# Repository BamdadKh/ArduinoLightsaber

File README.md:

# Arduino Lightsaber

A lightsaber prop built around an Arduino Nano on a custom PCB. It has a 144-LED blade,
sound from a DFPlayer Mini, swing detection with an MPU-6050, a small OLED and two buttons.
I built it for a Halloween costume.

*The OLED screens, rendered by the firmware's own UI code in a PC simulator.*

## Hardware

| | |
|---|---|
| Microcontroller | Arduino Nano (ATmega328P) |
| Motion | GY-521 (MPU-6050) on I²C |
| Sound | DFPlayer Mini, external amplifier and speaker |
| Blade | WS2812B strip, 144 LEDs, data on D6 |
| Buttons | main on D2, aux on D3 |
| Display | 0.91" SSD1306 128×32 OLED, software I²C on D8 (SDA) and D9 (SCL) |
| Power | one 18650 cell wired to the Nano's 5V pin, no boost converter |

The pin map, bill of materials and the known problems with the V3 board are in
[docs/hardware.md](docs/hardware.md). The schematic is in
[hardware/exports](hardware/exports/lightsaber-schematic.pdf). The schematic has mistakes the
board inherited; the firmware works around them, so trust the board and `docs/hardware.md`
over the schematic.

The hilt is modelled in Fusion 360 ([lightsaber-hilt.f3z](hardware/3d/lightsaber-hilt.f3z)),
and the printable tube is [hilt-tube.stl](hardware/3d/hilt-tube.stl), which GitHub shows in a
3D viewer.

## Building

You need [arduino-cli](https://arduino.github.io/arduino-cli/) with the `arduino:avr` core.
The sketch has no third-party libraries.

```bash
arduino-cli compile -b arduino:avr:nano firmware/lightsaber
arduino-cli upload -b arduino:avr:nano -p COM3 firmware/lightsaber
```

Nano clones with the old bootloader need `arduino:avr:nano:cpu=atmega328old`. The build uses
about 18 KB of the 30 KB of flash and 42% of RAM. Pins, LED count, current limit and the
battery and motion thresholds are in [config.h](firmware/lightsaber/config.h).

Building with `-DDEBUG_SERIAL=1` prints swing speed and battery voltage over USB at 115200 baud:

```bash
arduino-cli compile -b arduino:avr:nano --build-property "compiler.cpp.extra_flags=-DDEBUG_SERIAL=1" firmware/lightsaber
```

### SD card

```bash
pip install numpy
python firmware/tools/build_sd_card.py
```

This fills `firmware/sd-card/` and writes `sound_lengths.h`. Copy the `MP3` and `ADVERT`
folders to the root of a FAT32 micro-SD card. Details and the track list are in
[firmware/sd-card/README.md](firmware/sd-card/README.md).

### First run

1. If the screen is upside down, flip it in the menu.
2. Lay the saber still and run CALIBRATE in the menu. This zeroes the gyro. It also happens
   at power-up if the saber is lying still.
3. Compare the BATTERY page with a multimeter on the cell. If it's off, scale `BANDGAP_MV`
   in `config.h`; the Nano's voltage reference is only accurate to about 10%.

## Controls

| Blade off | |
|---|---|
| MAIN click | Ignite |
| AUX click, double click | Next colour, previous colour |
| AUX hold | Open the menu |

| Blade on | |
|---|---|
| MAIN click | Retract |
| AUX click | Blaster block |
| AUX hold | Lockup, until released |
| Swing | Swing sound (automatic) |

| Menu | |
|---|---|
| AUX click, double click | Next page, previous page |
| MAIN click | Change the value or run the action |
| AUX hold | Save and exit |

The menu pages are sound, light, colour, sensitivity, flip, calibrate, battery and exit.
Light and colour preview on the blade. The saber retracts by itself after five minutes
without movement.

## How it works

The blade is rendered per pixel into the LED array, which is the only frame buffer in the
sketch. The OLED has none either. The panel is mounted on its side and driven in vertical
addressing mode, so one physical column is one 32-pixel row of the portrait screen. Each
screen is a function that returns a row as a `uint32_t`, and the UI streams a few rows per
`loop()` pass.

The LED strip needs interrupts off for about 4 ms per frame, which rules out serial
receive. The DFPlayer is therefore driven blind. The hum loops on the main channel,
effects play as DFPlayer adverts that pause and then resume it, and the one-shot lengths are
compiled in so the firmware can stop them when they end.

The cell feeds the Nano's supply directly, so the supply voltage is the cell voltage. The
firmware measures it against the internal 1.1 V reference. Charge level and warnings use the
voltage with the blade off, because the strip pulls it down by several tenths of a volt when lit.

| Module | Job |
|---|---|
| `saber.cpp` | modes and controls |
| `imu.cpp` | MPU-6050 reading and swing detection |
| `blade.cpp` | blade colours, ignition and effects |
| `color.cpp` | WS2812B driver, current limit |
| `ui.cpp`, `gfx.h`, `oled.cpp` | OLED screens and display driver |
| `audio.cpp` | DFPlayer protocol and sound playback |
| `buttons.cpp` | debouncing, clicks, holds |
| `power.cpp` | battery voltage |
| `settings.cpp` | EEPROM settings, colour table |

## Repository

```
firmware/lightsaber/   the sketch
firmware/sd-card/      sounds for the DFPlayer
firmware/tools/        asset and SD card builders, PC simulator
hardware/kicad/        KiCad 8 project
hardware/fabrication/  gerbers exactly as ordered (V3)
hardware/exports/      schematic PDF, PCB renders
hardware/3d/           hilt model, tube STL, PCB STEP
docs/                  hardware notes, images
```

The simulator runs the real `ui.cpp` and `blade.cpp` on a PC (it needs MSYS2 g++ or MSVC):

```bash
python firmware/tools/sim/run_sim.py
python firmware/tools/make_readme_images.py
```

*Blade timelines from the simulator. Time runs left to right and the hilt is at the bottom.*

## Credits

The blade sounds come from the TeensySF font in the
[ProffieOS](https://fredrik.hubbe.net/lightsaber/) default SD card, by Fredrik Hubinette
([CC BY-SA 4.0](https://creativecommons.org/licenses/by-sa/4.0/)). The menu and boot sounds
are synthesized by the repository's tools.

## License

[MIT](LICENSE). The sound files are under their own licence, see above.

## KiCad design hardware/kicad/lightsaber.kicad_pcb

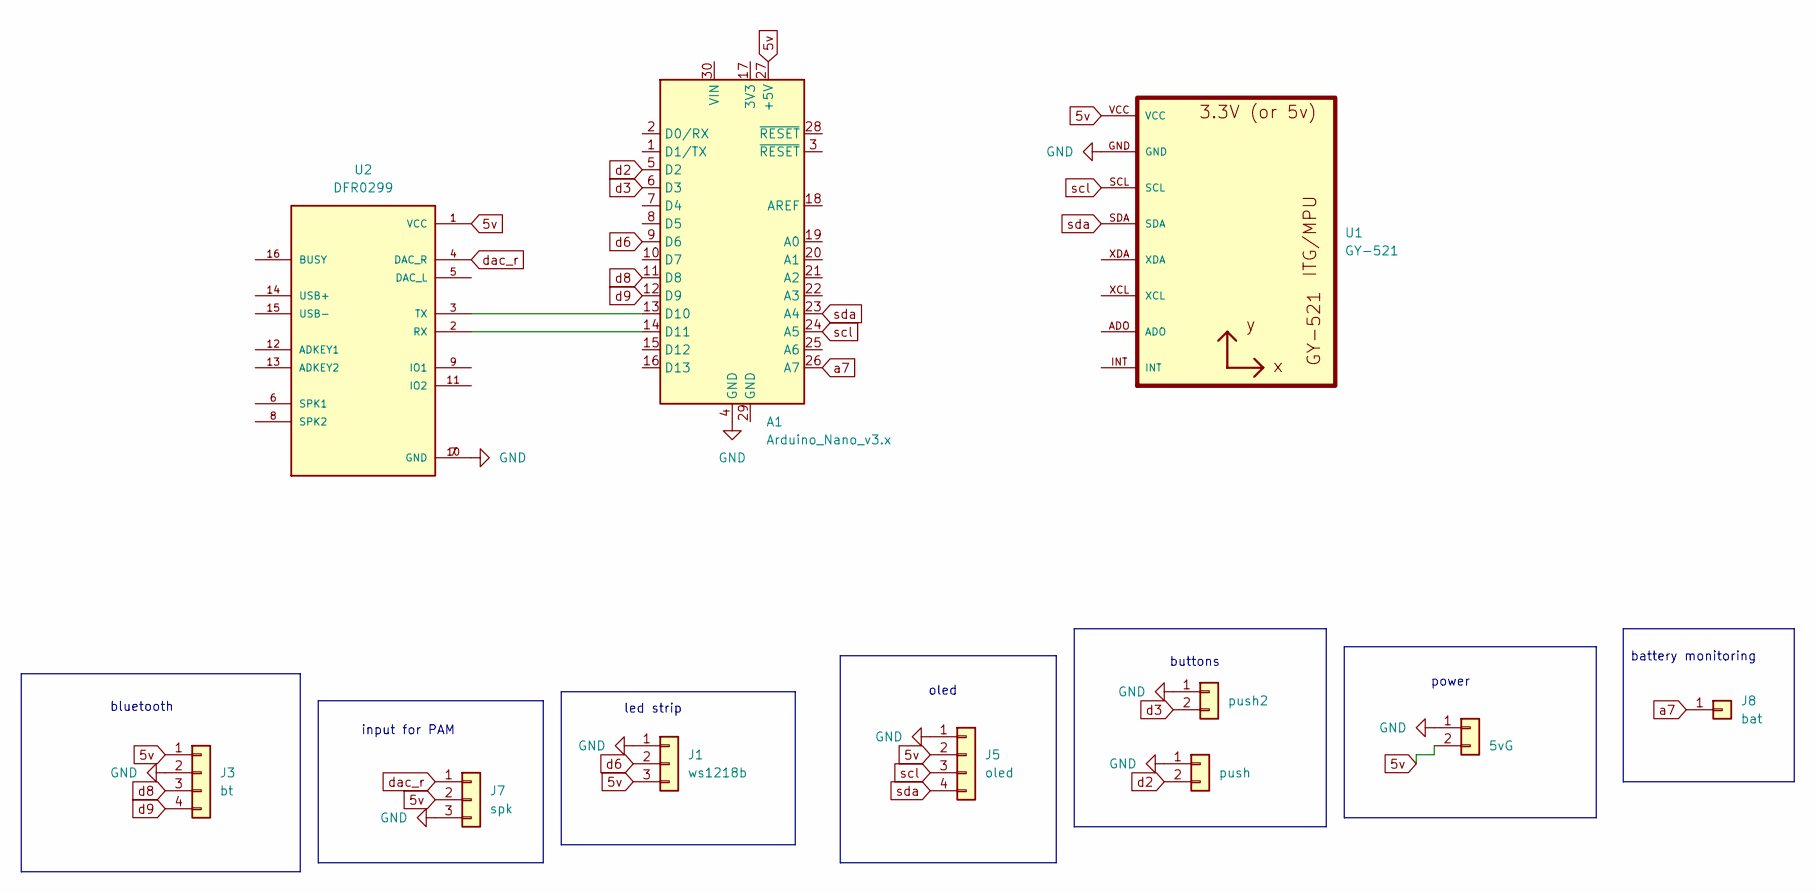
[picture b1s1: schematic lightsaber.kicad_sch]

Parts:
A1: Arduino_Nano_v3.x; Arduino_Nano
J1: ws1218b; PinHeader_1x03_P1.00mm_Vertical
J2: push; PinHeader_1x02_P1.00mm_Vertical
J3: bt; PinHeader_1x04_P1.27mm_Vertical
J4: push2; PinHeader_1x02_P1.00mm_Vertical
J5: oled; PinHeader_1x04_P1.27mm_Vertical
J6: 5vG; PinHeader_1x02_P1.00mm_Vertical
J7: spk; PinHeader_1x03_P1.00mm_Vertical
J8: bat; PinHeader_1x01_P1.00mm_Vertical
U1: GY-521
U2: DFR0299; MODULE_DFR0299

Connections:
5v: A1.27 (+5V), J1.3, J3.1, J5.2 (vcc), J6.2 (5v), J7.2, U1.VCC, U2.1 (VCC)
GND: A1.4 (GND), J1.1, J2.1 (G), J3.2, J4.1 (G), J5.1 (gnd), J6.1 (G), J7.3, U1.GND, U2.7 (GND), U2.10 (GND)
unnamed: A1.13 (D10), U2.3 (TX)
unnamed: A1.14 (D11), U2.2 (RX)
a7: A1.26 (A7), J8.1
d2: A1.5 (D2), J2.2 (dat)
d3: A1.6 (D3), J4.2 (dat)
d6: A1.9 (D6), J1.2
d8: A1.11 (D8), J3.3
d9: A1.12 (D9), J3.4
dac_r: J7.1, U2.4 (DAC_R)
scl: A1.24 (A5), J5.3 (sck), U1.SCL
sda: A1.23 (A4), J5.4 (sda), U1.SDA

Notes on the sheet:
bluetooth
input for PAM
power
led strip
buttons
oled
battery monitoring

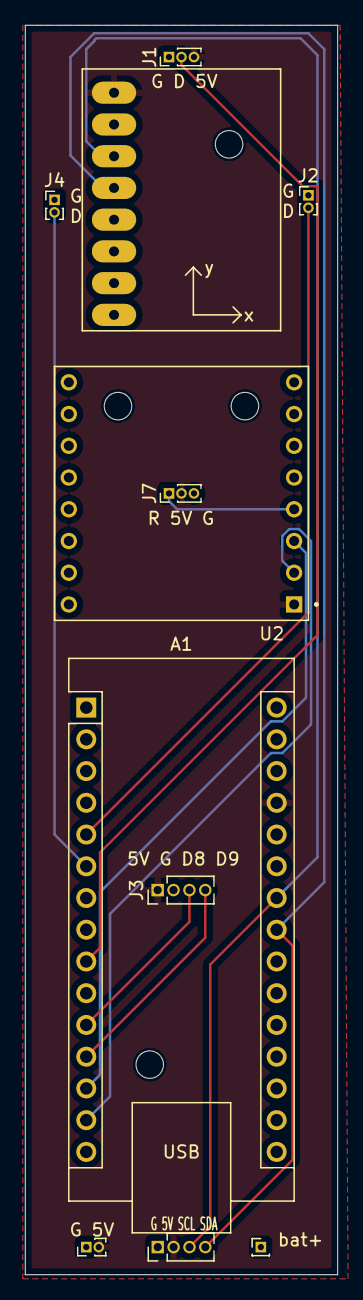
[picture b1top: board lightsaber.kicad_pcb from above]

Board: 2 copper layers, 25.0 x 100.0 mm, 11 parts (0 on the bottom side), 13 nets.
